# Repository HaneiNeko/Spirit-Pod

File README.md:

# SpiritPod

## What is a SpritPod ?
The SpiritPod is a device used by ghost hunters to detect ghosts, spirits, and demons. 😈👻

## How does it work ?
It's like an EMF detector (https://github.com/HaneiNeko/EMF-Detector 🙃), the SpiritPod work with a antenna, if an electromagetics field touch the antenna, a LED will be turn ON, and a beep from a buzzer will be heard.

## This project
This project use the Arduino framework.

## Schematics

## Usage
1. Use the schematic for create the PCB
2. Push the code into the microcontroller
3. Print the case (optional)
4. Enjoy ! 👻😉

## Real SpiritPod

## Other similar project 😉
This amazing project from 
Mancave Effects : https://www.youtube.com/watch?v=FR6dkNfYyT0

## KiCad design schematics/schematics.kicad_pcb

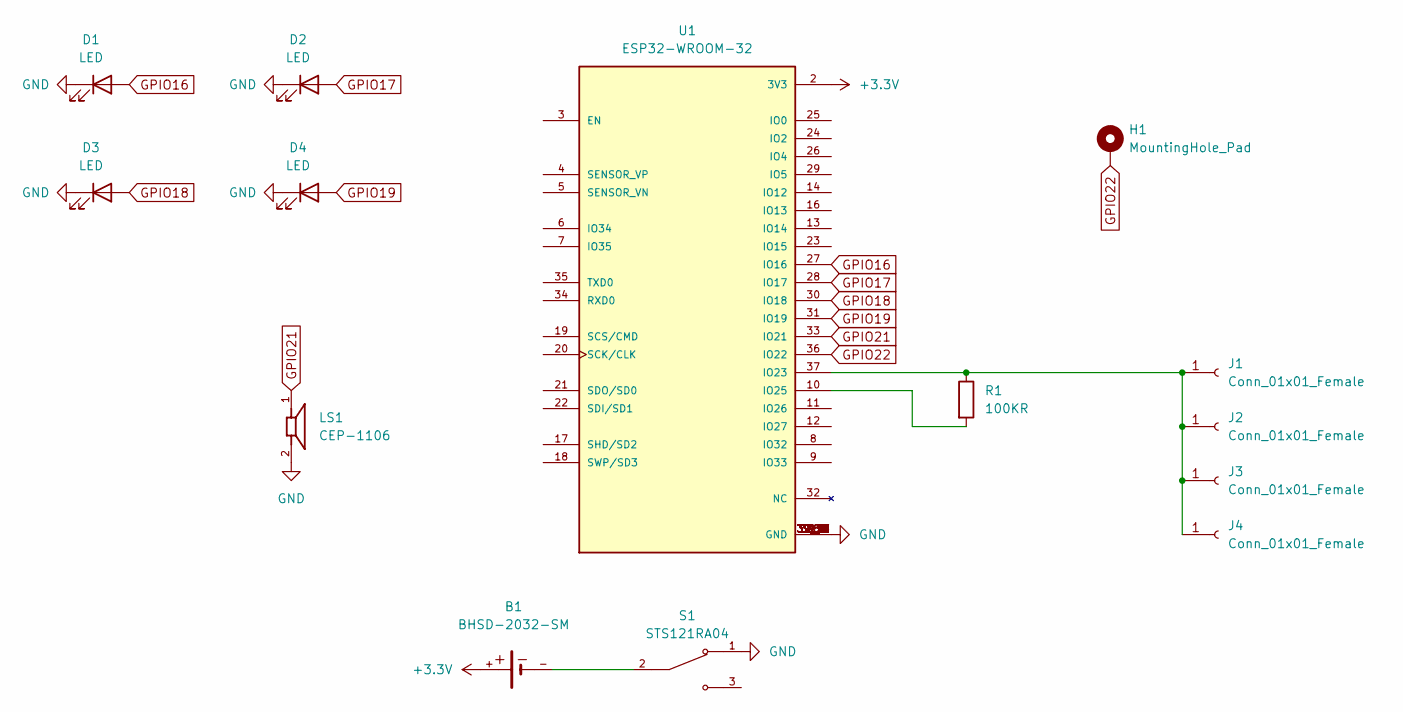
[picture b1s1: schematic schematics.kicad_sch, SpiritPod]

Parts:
B1: BHSD-2032-SM
D1, D2, D3, D4: LED; LED_D5.0mm
H1: MountingHole_Pad; MountingHole_3mm_Pad
J1, J2, J3, J4: Conn_01x01_Female; PinHeader_1x01_P1.00mm_Vertical
LS1: CEP-1106; CUI_CEP-1106
R1: 100KR; R_Axial_DIN0309_L9.0mm_D3.2mm_P12.70mm_Horizontal
S1: STS121RA04; TE_STS121RA04; PARTREV A3
U1: ESP32-WROOM-32; MODULE_ESP32-WROOM-32; PARTREV 2.9

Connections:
+3.3V: B1.+, U1.2 (3V3)
GND: D1.1 (K), D2.1 (K), D3.1 (K), D4.1 (K), LS1.2, S1.1, U1.1 (GND), U1.15 (GND), U1.38 (GND), U1.39_1 (GND), U1.39_2 (GND), U1.39_3 (GND), U1.39_4 (GND), U1.39_5 (GND), U1.39_6 (GND), U1.39_7 (GND), U1.39_8 (GND), U1.39_9 (GND), U1.39_10 (GND), U1.39_11 (GND), U1.39_12 (GND), U1.39_13 (GND), U1.39_14 (GND), U1.39_15 (GND), U1.39_16 (GND), U1.39_17 (GND), U1.39_18 (GND), U1.39_19 (GND), U1.39_20 (GND), U1.39_21 (GND)
GPIO16: D1.2 (A), U1.27 (IO16)
GPIO17: D2.2 (A), U1.28 (IO17)
GPIO18: D3.2 (A), U1.30 (IO18)
GPIO19: D4.2 (A), U1.31 (IO19)
GPIO21: LS1.1, U1.33 (IO21)
GPIO22: H1.1, U1.36 (IO22)
unnamed: B1.-, S1.2
unnamed: J1.1, J2.1, J3.1, J4.1, R1.1, U1.37 (IO23)
unnamed: R1.2, U1.10 (IO25)

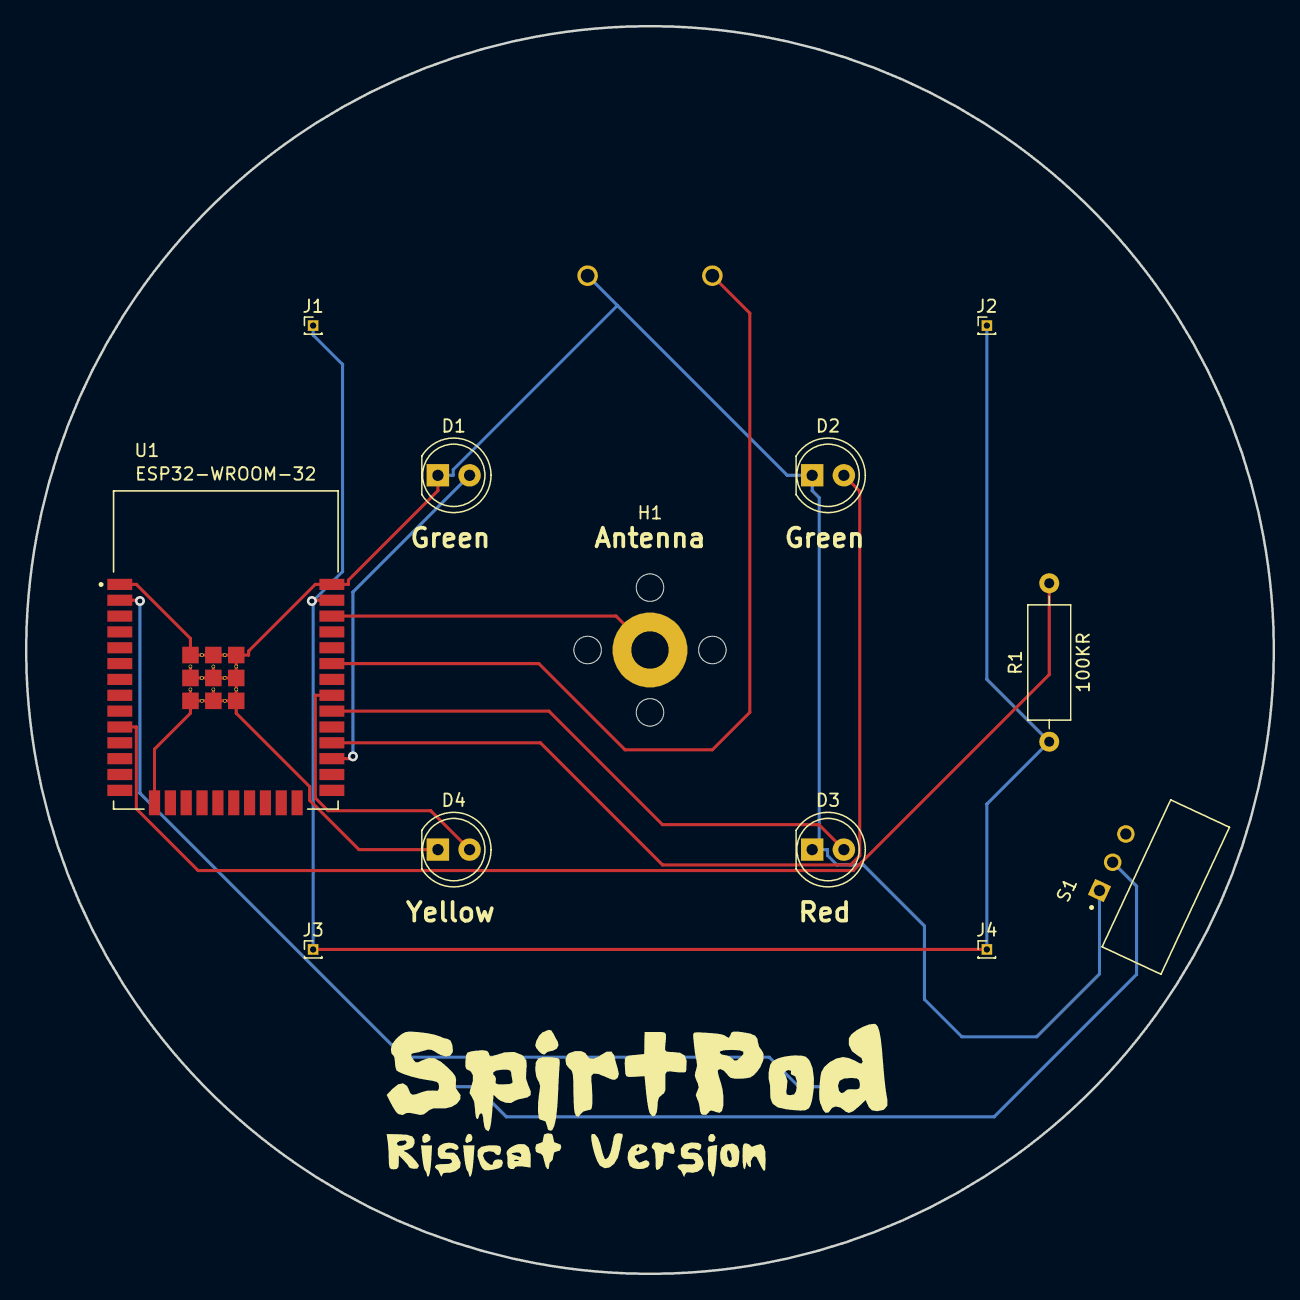
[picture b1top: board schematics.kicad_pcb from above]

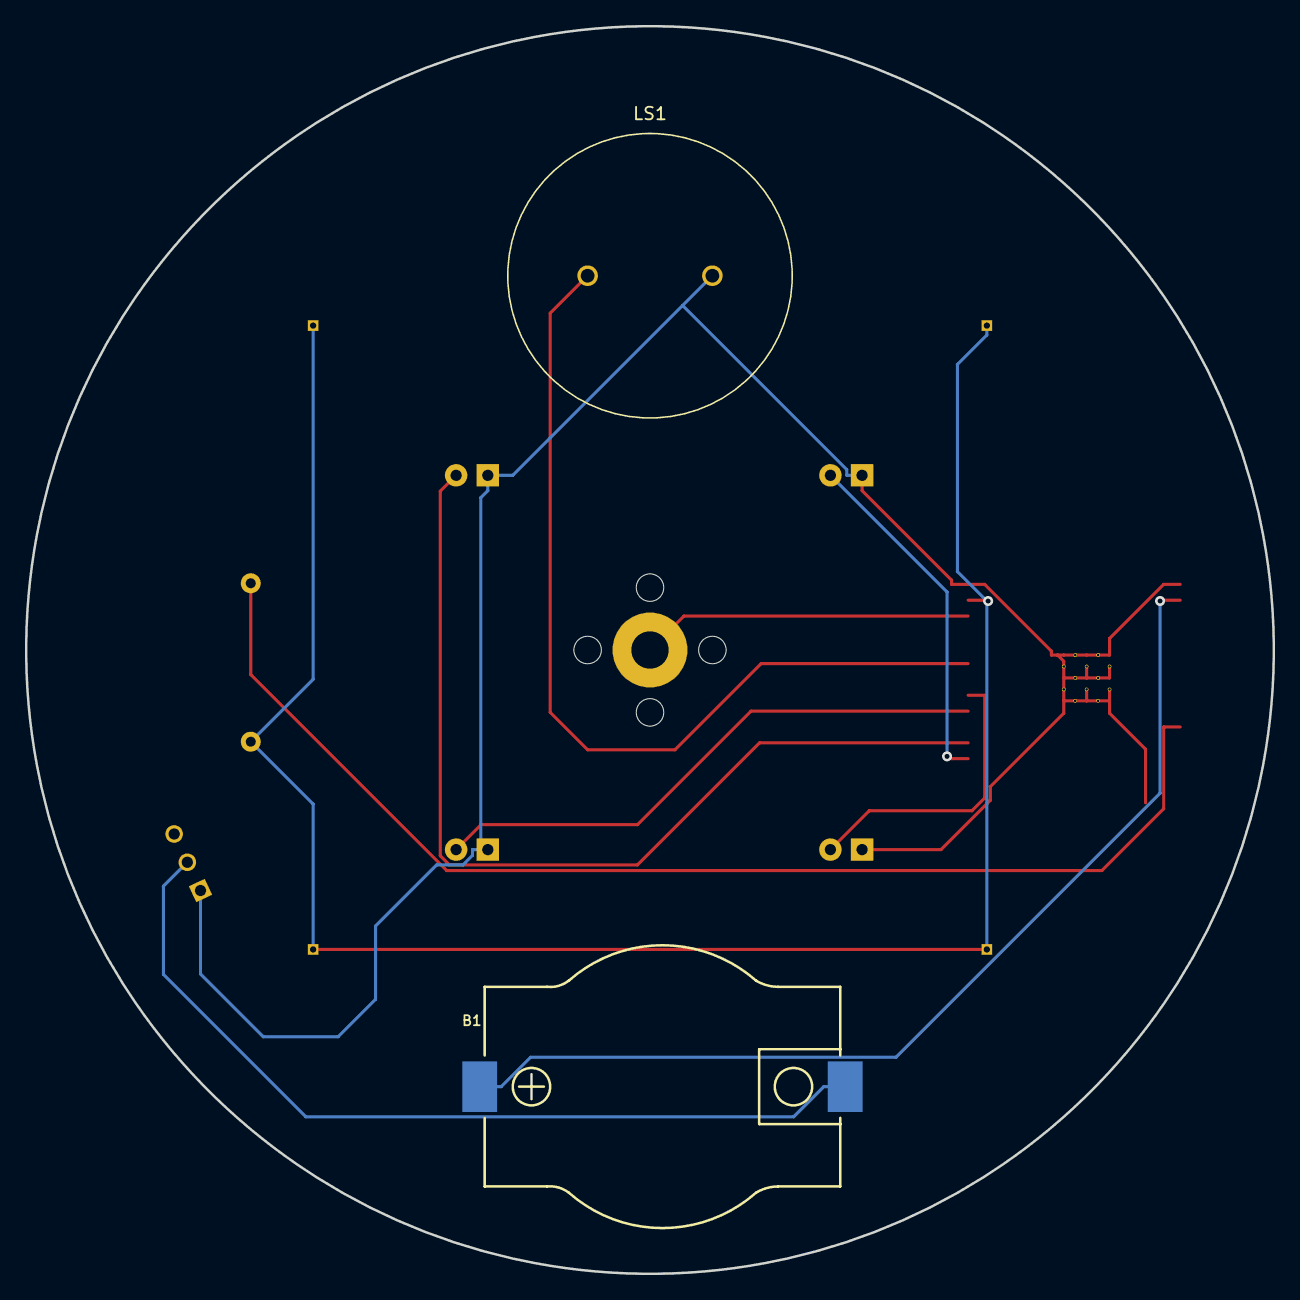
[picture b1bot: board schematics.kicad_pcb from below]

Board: 2 copper layers, 100.0 x 100.0 mm, 14 parts (2 on the bottom side), 11 nets.

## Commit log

2025-06-18 Create readme file
2025-06-18 Add images
2025-06-18 Add images to the readme file
2025-06-18 Add badges to the readme file
2025-06-20 Add the logo
2025-06-20 Add the logo file
2025-06-20 Add the schematics
2025-06-20 Add the schematics image to the readme
2025-06-20 Add the schematics image
2025-06-20 Add similar project
